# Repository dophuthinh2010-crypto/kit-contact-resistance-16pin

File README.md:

# Kit: 16-pin connector contact resistance tester

Test kit that measures the mated contact resistance of all 16 contacts of an
ITW McMurdo Red Range 16-way connector (RP16-T plug / RS16P-T socket) after
every plug/unplug cycle. The data is used to estimate connector life
(datasheet: 5 mΩ max initially, 10 mΩ max after conditioning, 500 mechanical operations).

**Status:** design stage, for review. Firmware and desktop app written (app core tested; firmware and GUI not yet run on hardware). Schematic and PCB layout not yet drawn in KiCad.

## How it works

- ESP32 selects one contact at a time (16 low-side MOSFETs driven by 2 × 74HC595).
- An LM317T constant-current source drives 0.625 A through the selected contact; a 0.1 Ω shunt read by
  the ADS1115 gives the current I. (Main board rev C.)
- Kelvin sense taps at the connector pads go through two 16-to-1 trees of CD4053BE switches straight to
  the ADS1115, read differentially at ±0.256 V (7.8 µV per step): contact voltage V.
- R = V / I. Range is about 0–51 mΩ (G = 101) or 0–470 mΩ (G = 11, jumper).
- One CSV line per pin per cycle over USB serial: `cycle, pin, I_A, V_mV, R_mOhm`.

Boards: main board (100 × 80 mm, 2-layer) plus two jack breakouts (about 80 × 40 mm),
linked by 34-way IDC ribbons (16 force + 16 sense + 2 GND).

## Repository layout

| Path | Contents |
| --- | --- |
| `docs/INSTALL.md` | **Start here:** installing the USB driver, the desktop app and the firmware, then running a test |
| `docs/design.md` | Design summary: schematic blocks, pin map, connector pinouts, layout rules, open items |
| `docs/concept_sketch.jpg` | System concept diagram (redrawn from the original sketch, `docs/concept_sketch_original.jpg`; source: `hardware/scripts/draw_concept_diagram.py`) |
| `docs/footprint_preview.png` | Preview of the connector footprints |
| `docs/CR-TEST_presentation.pptx` | 13-slide PowerPoint presentation of the kit (source: `docs/presentation/build_deck.js`, pptxgenjs) |
| `docs/3d-model/index.html` | Interactive 3D model of the kit (open in a browser; loads three.js from a CDN) |
| `docs/fault-protection.md` | Open/short fault review, isolation test, rev C protection, scenario results |
| `docs/serial-protocol.md` | Serial protocol between the ESP32 and the laptop |
| `firmware/crkit_esp32/` | ESP32 firmware (Arduino): scan, mate detect, calibration |
| `desktop-app/` | Desktop app (Python, PySide6): connect, record to CSV, live table and plot |
| `docs/simulation/index.html` | 3D simulation: plug/unplug cycles, 16-pin scan through the rev C LM317T / CD4053B / ADS1115 chain with noise, assumed wear model and life estimate |
| `hardware/BOM.xlsx`, `hardware/BOM.csv` | Bill of materials for one kit (rev C, $156.22): model, supplier, price, alternative part (shared sheet: https://claude.ai/artifact/EmcHuasxRLR5GvdHxSPXVu) |
| `hardware/kicad/` | **Rev C KiCad 8 projects**: main board (schematic + placed PCB), female and male jack boards, shared libraries, previews. Not routed yet: see `hardware/kicad/README.md` |
| `hardware/scripts/kicad_gen/` | Python generator for those projects (`python build_all.py`) |
| `hardware/footprints/McMurdo_RedRange.pretty/` | KiCad footprints for RP16-T and RS16P-T |
| `hardware/scripts/gen_mcmurdo_fp.py` | Script that generates those footprints |

The full, living design document (with the BOM and block diagram) is the Claude doc
"PCB Design – 16-Pin Blindmate Contact Resistance Test Kit":
https://claude.ai/artifact/T8kFqe1HFXj3PjpiL8ypHh

## Connector reference

ITW McMurdo "Red range" industrial rack and panel connectors datasheet (not included in
this repo; get it from ITW McMurdo or a distributor).

## Using the footprints

KiCad → Preferences → Manage Footprint Libraries → add
`hardware/footprints/McMurdo_RedRange.pretty`.

## Next steps

- [ ] Review the design summary and open items
- [x] Schematic rev C in KiCad (LM317T, CD4053BE, ADS1115; main board + jack boards, generated)
- [x] PCB placement, nets, net classes, outlines, GND pours
- [ ] Open in KiCad 8, run ERC/DRC, route (hand-route power, Freerouting for the rest)
- [ ] Check footprints against real parts, then order PCBs
- [x] Firmware: scan loop, calibration, serial protocol
- [x] Desktop app: recording, live view, resume, summary
- [ ] Test firmware and app on the real kit

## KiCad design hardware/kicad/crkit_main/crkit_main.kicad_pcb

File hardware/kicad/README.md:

# KiCad projects, board rev C

| Folder | Board | Size | Status |
| --- | --- | --- | --- |
| `crkit_main/` | Main board: LM317T current source, 16 pin switches, 10× CD4053BE sense muxes, ADS1115, ESP32-DevKitC socket | 135 × 101 mm, 2 layers, 2 oz | Schematic complete. PCB placed, nets and net classes set, GND pours on both layers. **Not routed** |
| `crkit_jack_female/` | RS16P-T socket + 2×17 IDC | 80 × 40 mm | Schematic complete. PCB placed. **Not routed** |
| `crkit_jack_male/` | RP16-T plug + 2×17 IDC | 80 × 40 mm | Schematic complete. PCB placed. **Not routed** |
| `crkit.kicad_sym`, `crkit.pretty/` | Symbols and footprints used by all three (also embedded in each file) | | |
| `preview/` | PNG previews of the schematic and of each placement with its ratsnest | | |

All files are written by `hardware/scripts/kicad_gen/build_all.py` (KiCad 8 format). The design lives
in the scripts: `main_board.py` (netlist + placement), `jack_board.py`, `lib.py` (symbols and footprints).
To change the design, edit the script and run `python build_all.py`, or open the files in KiCad and keep
editing there (then stop regenerating, or your KiCad edits will be overwritten).

The files were generated without KiCad (no KiCad in the build environment). They follow the KiCad 8 file
format and pass a structural check, but **open them in KiCad 8 or newer and run ERC and DRC before
anything else.** Schematic style: every part is a box symbol, and every pin ends in a short wire with
a net label, so the netlist is exact and easy to check against `docs/design.md`.

## Rev C changes (23 Nov 2026)

| Change | Parts |
| --- | --- |
| Test current from an **LM317T** constant-current source: R_SET 2.0 Ω 3 W → 0.625 A. Replaces R_HI, R_LO and the ACS712 | U2, R4, C4, C5 |
| Current measured on a **0.1 Ω 1 % shunt** (2512) by the ADS1115 (AIN2−AIN3, Kelvin taps) | R5, R74, R75, C19 |
| Sense muxes: two 16-to-1 trees of **CD4053BE** (15 switches each: S0 / S1 / S2 / S3 by level) replace the CD74HC4067s | U5–U9 (female), U10–U14 (male), C8–C17 |
| **INA333, OPA333 REF buffer and gain jumper removed**: the ADS1115 reads the contact differentially at ±0.256 V | U15, R72, R73, C18, D3, D4 |
| 32 BAT54S input clamps removed: 10 kΩ per sense line into the 3.3 V muxes (bleeder R70), clamps only at the ADC | R38–R70 |
| 5 V monitor moved from ADS1115 AIN2 to ESP32 IO34 | R79, R80, C21 |
| Board 135 × 90 → 135 × 101 mm | |

Rev B changes still in place: reverse-polarity MOSFET (Q1), 10 kΩ sense resistors, 3.3 kΩ bleeder,
ribbon pins 33/34 not connected.

## Reference map (docs → KiCad references)

| Docs | KiCad | Docs | KiCad |
| --- | --- | --- | --- |
| Q_REV | Q1 | Q_DRV 2N7002 | Q2 |
| Q_EN AO3401A | Q3 | Pin switches 1…16 | Q4…Q19 (contact n = Q(n+3)) |
| LM317T | U2 | R_SET 2.0 Ω / R_SH 0.1 Ω | R4 / R5 |
| AP2112K LDO | U1 | 74HC595 ×2 | U3, U4 |
| CD4053BE female tree | U5–U9 | CD4053BE male tree | U10–U14 |
| ADS1115 | U15 | ESP32-DevKitC | U16 |
| Barrel jack | J1 | IDC to female / male board | J2 / J3 |
| Mate switch | J4 | I²C spare | J5 |
| Sense resistors 10 k | R38–R69 | Test points | TP1 LO_RTN, TP2 GND, TP3 F_BUS, TP4 SENSE_F, TP5 SENSE_M, TP6 V5_MON |

## Main board placement

- Top: LM317T (U2, vertical TO-220 with a clip-on heatsink), R_SET (R4, mount 2 mm off the board),
  current switch Q2/Q3, shunt R5, shift registers U3/U4.
- Left: power input (J1 on the board edge, Q1 reverse protection, F1, D2 TVS, C1, LDO U1).
- Centre: two rows of 8 pin switches with their gate resistors and pull-downs.
- Middle: ADS1115 (U15) with its input filters and clamps, pull-ups, 5 V monitor, test points.
- Lower: one row of ten CD4053BE, female tree on the left (U5–U9), male tree on the right (U10–U14),
  a 100 nF decoupler beside each.
- Bottom: 10 k sense resistors straight above their IDC columns. J2/J3 are turned 180° so the sense row
  faces the resistors. **Pin 1 is at the right-hand end** of both headers.
- Right: ESP32-DevKitC on two 1×19 sockets 25.4 mm apart, USB end over the top edge.

## Routing (next step)

Net classes are set in the project: **Power** 1.0 mm / 0.3 mm (F_BUS, LO_RTN, I_HI, ACS_IP, +5V, VIN_*,
MF1–MF16, GND, LM_IN, LM_OUT) and **Sense** 0.25 mm (SF/SM, SFC/SMC, tree nodes, SENSE_F/M, ADS and shunt taps). Default 0.25 mm / 0.2 mm.

1. Open `crkit_main.kicad_pro` in KiCad 8+. Run **Inspect → Electrical Rules Checker** on the schematic, then
   **Tools → Update PCB from Schematic** (should report no changes) and **DRC** (unrouted only).
2. Route by hand first: F_BUS (R_SET/LM317T ADJ → J2 odd row) and LO_RTN (16 sources → R5) as wide pours or 1.5 mm
   traces on the top layer; the R5 return goes straight to the J1 ground, and the two R5 ADC taps are separate thin traces.
3. Then autoroute the rest: **File → Export → Specctra DSN**, route it in Freerouting, then
   **File → Import → Specctra Session**. Keep SENSE_F and SENSE_M as a tight pair over unbroken ground.
4. Press **B** to refill the GND pours and run DRC again.
5. Jack boards: the force (odd) and sense (even) trace of each contact must leave the pad on opposite sides
   and meet only at the pad. Contacts 9–16 are on the far row, so use both layers.

## Check before ordering PCBs

- Footprints against real parts: RP16-T / RS16P-T sample, CUI PJ-002A barrel jack drawing,
  your ESP32-DevKitC (row spacing 25.4 mm, pinout of V4), the LM317T heatsink outline, the 3 W R_SET lead spacing.
- ERC, DRC, and a 1:1 paper print of each board with the connector and the DevKitC laid on it.

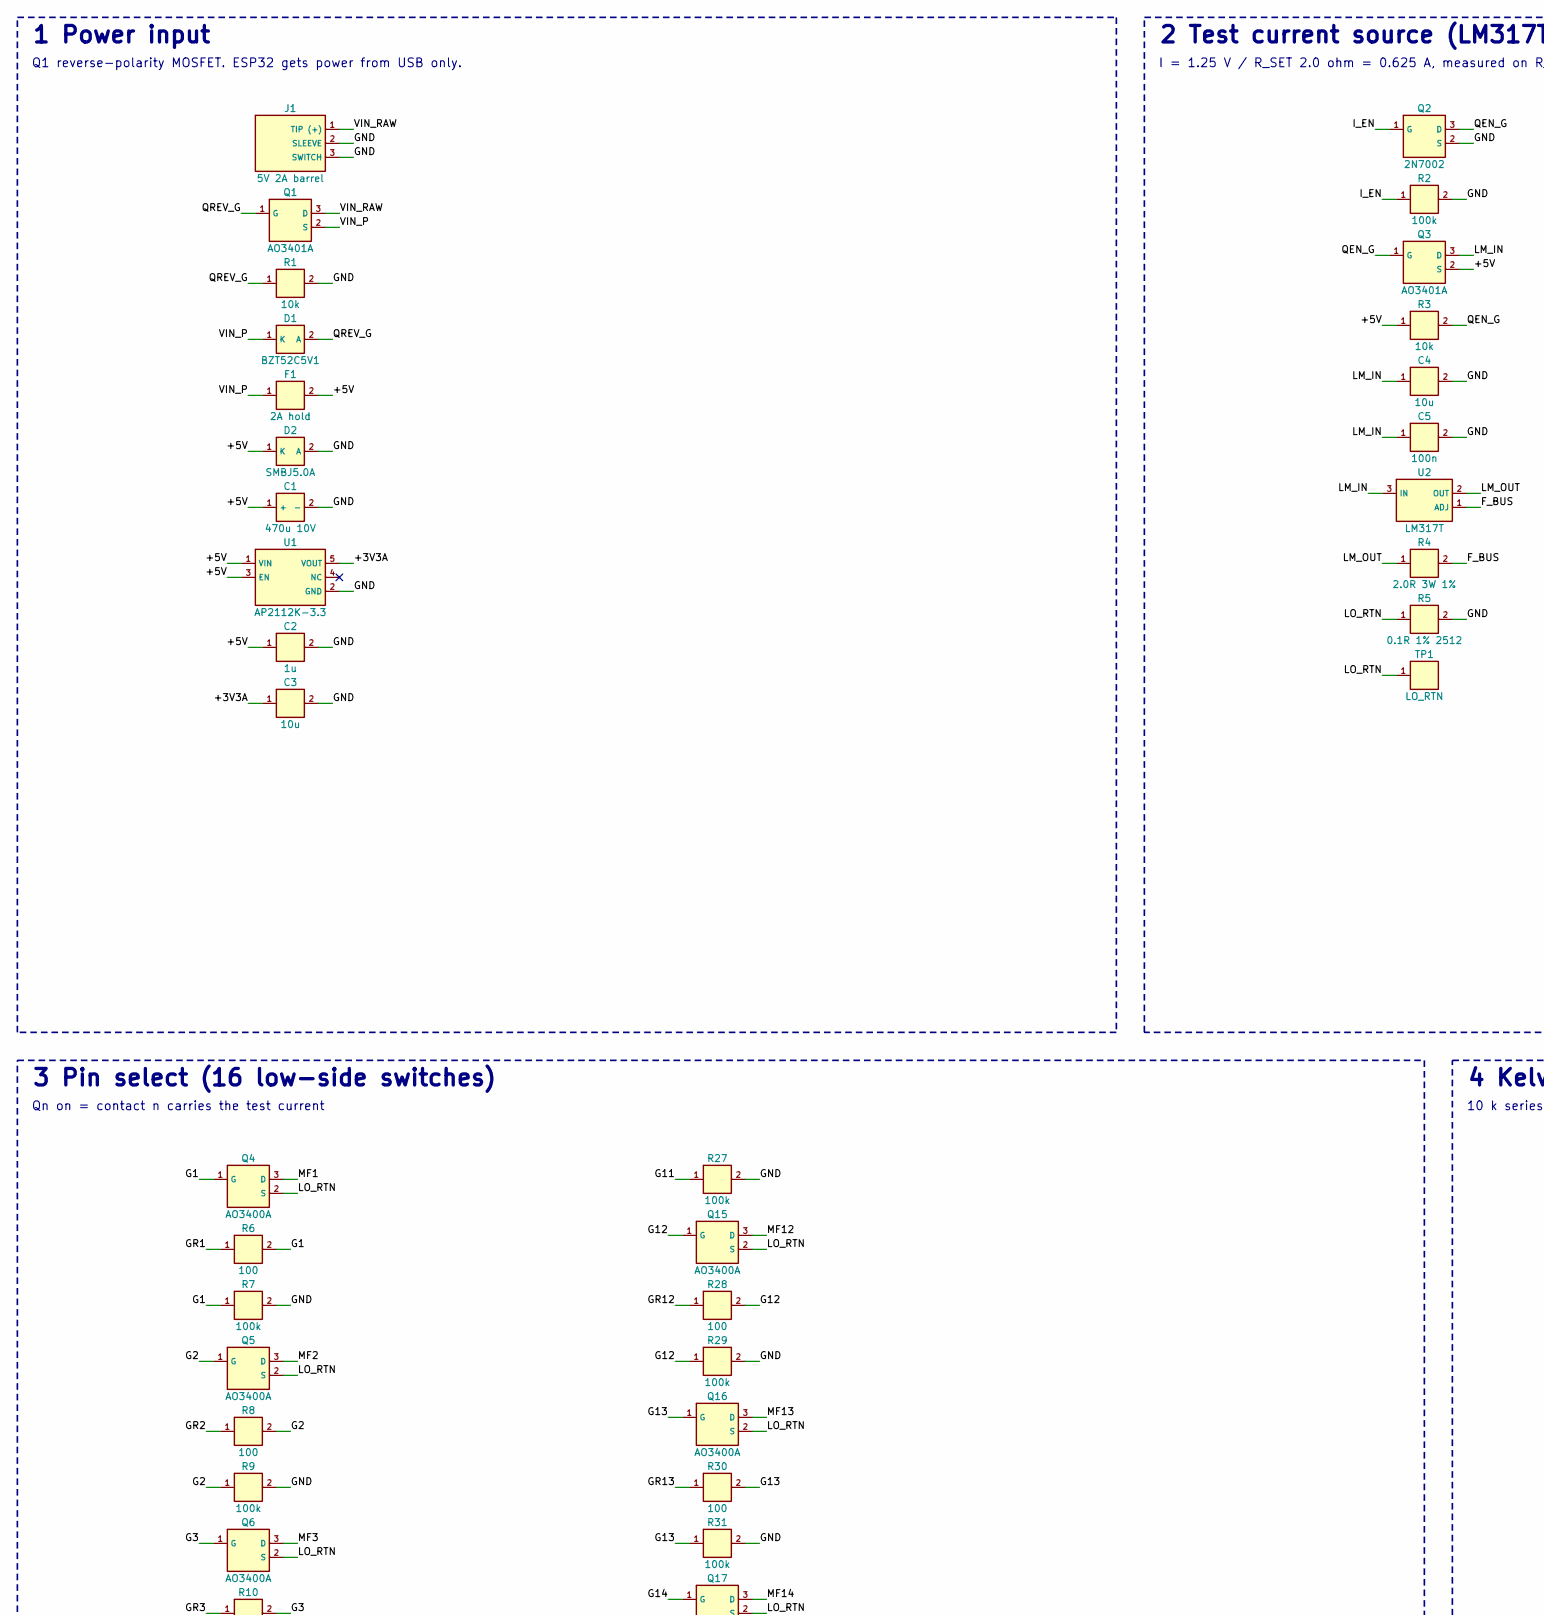
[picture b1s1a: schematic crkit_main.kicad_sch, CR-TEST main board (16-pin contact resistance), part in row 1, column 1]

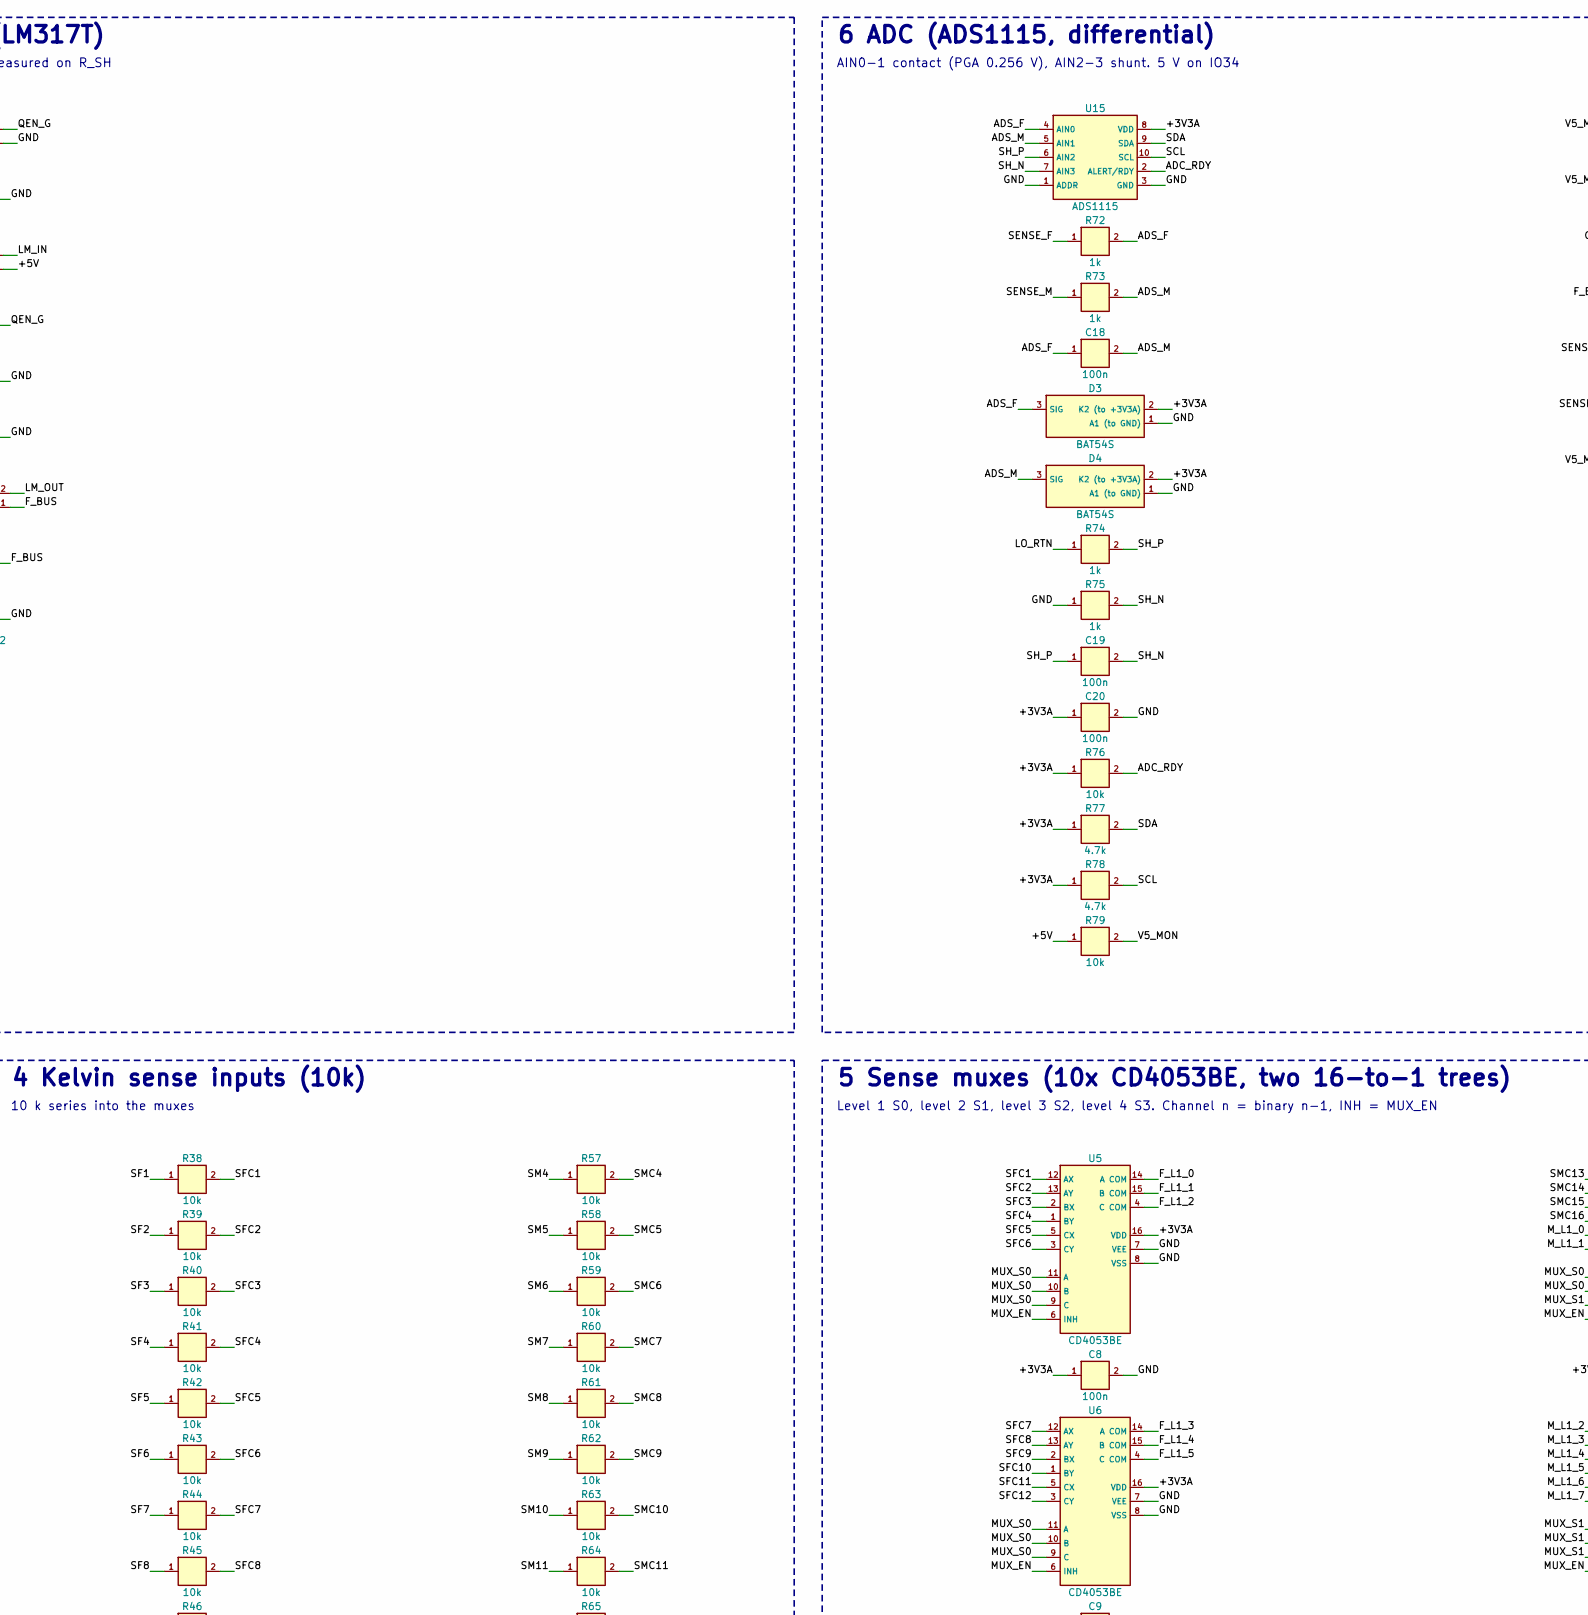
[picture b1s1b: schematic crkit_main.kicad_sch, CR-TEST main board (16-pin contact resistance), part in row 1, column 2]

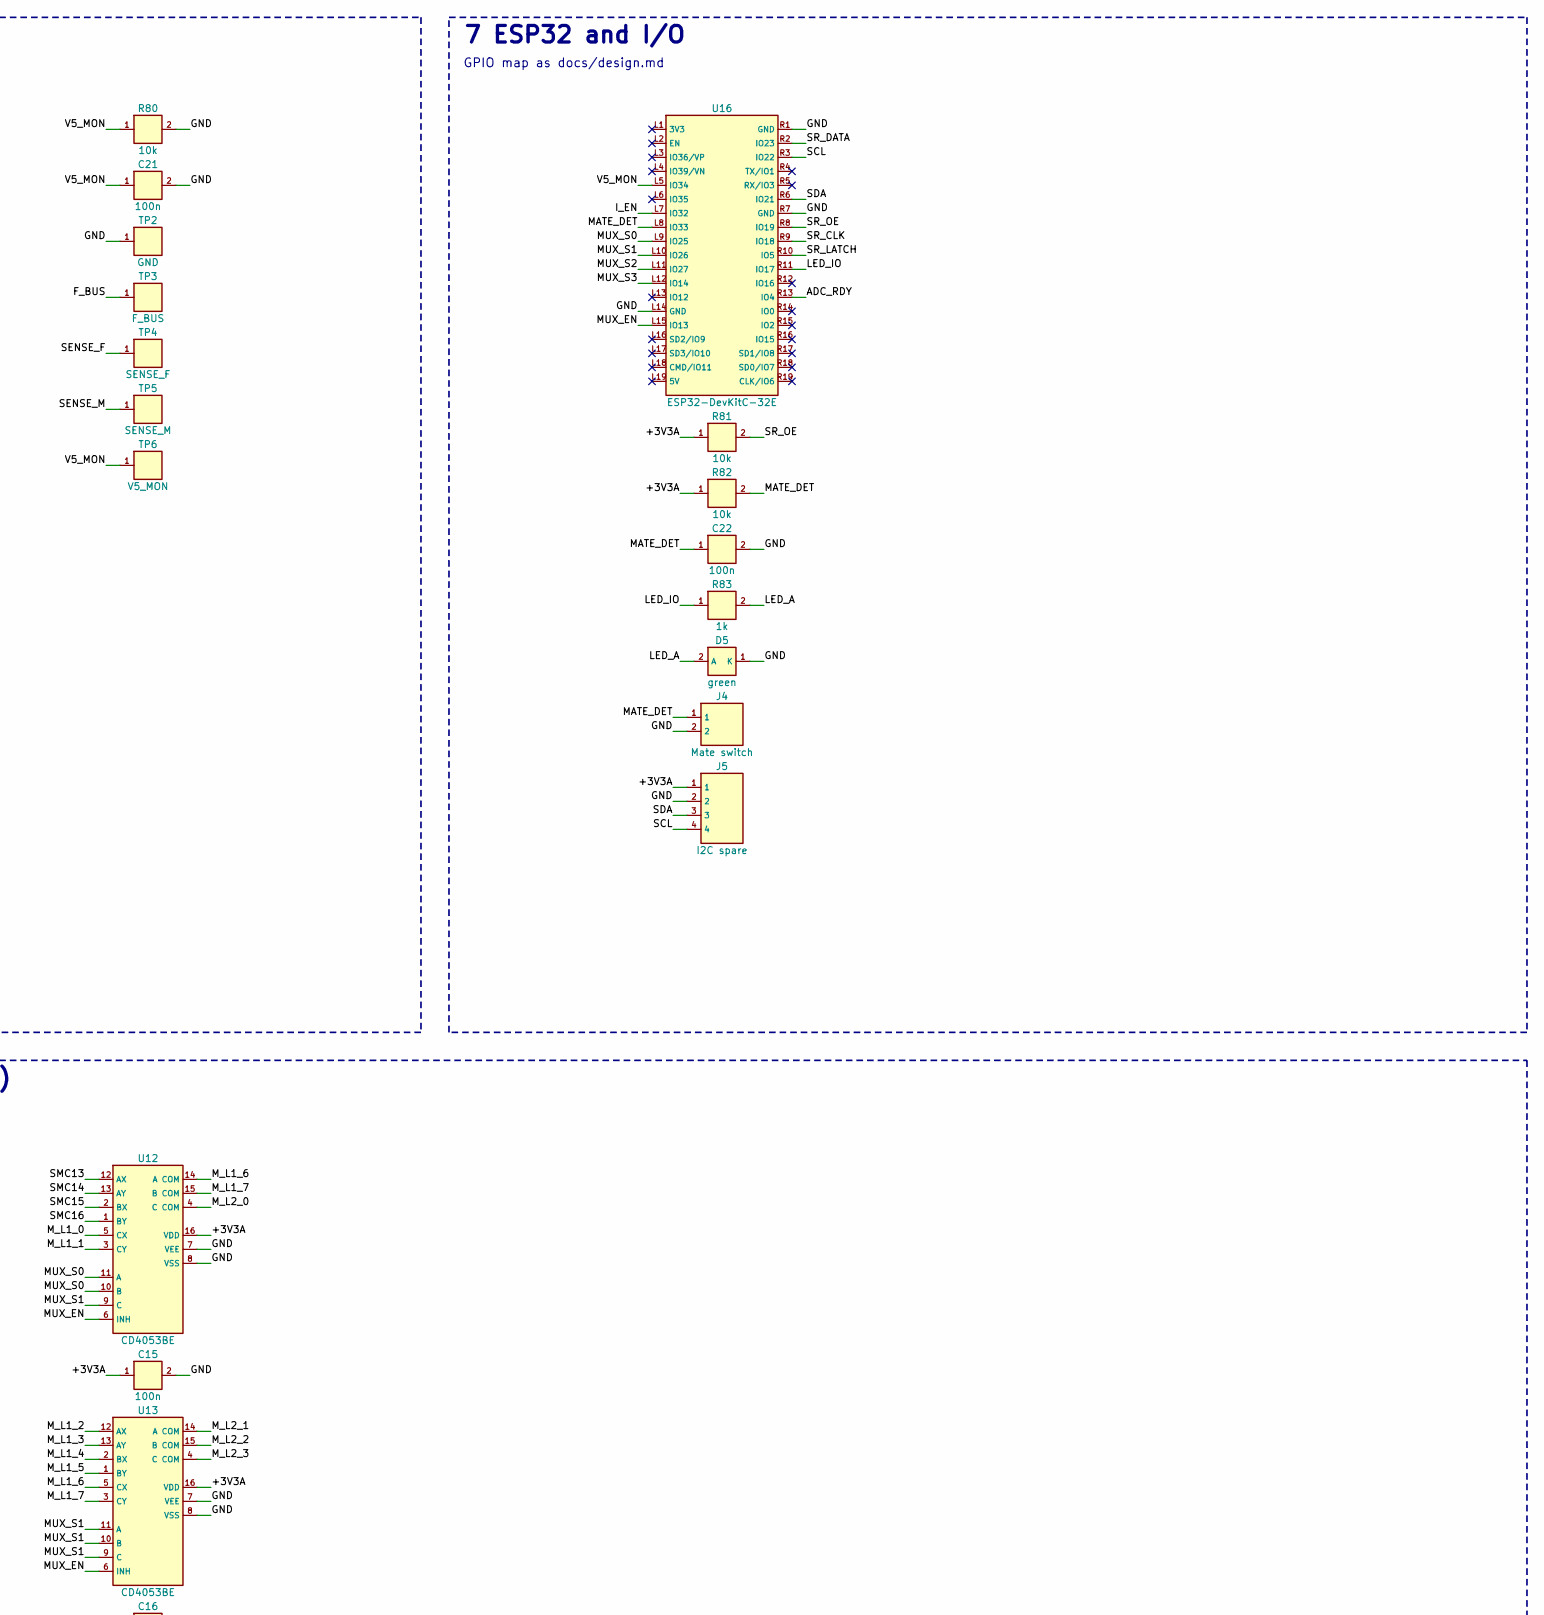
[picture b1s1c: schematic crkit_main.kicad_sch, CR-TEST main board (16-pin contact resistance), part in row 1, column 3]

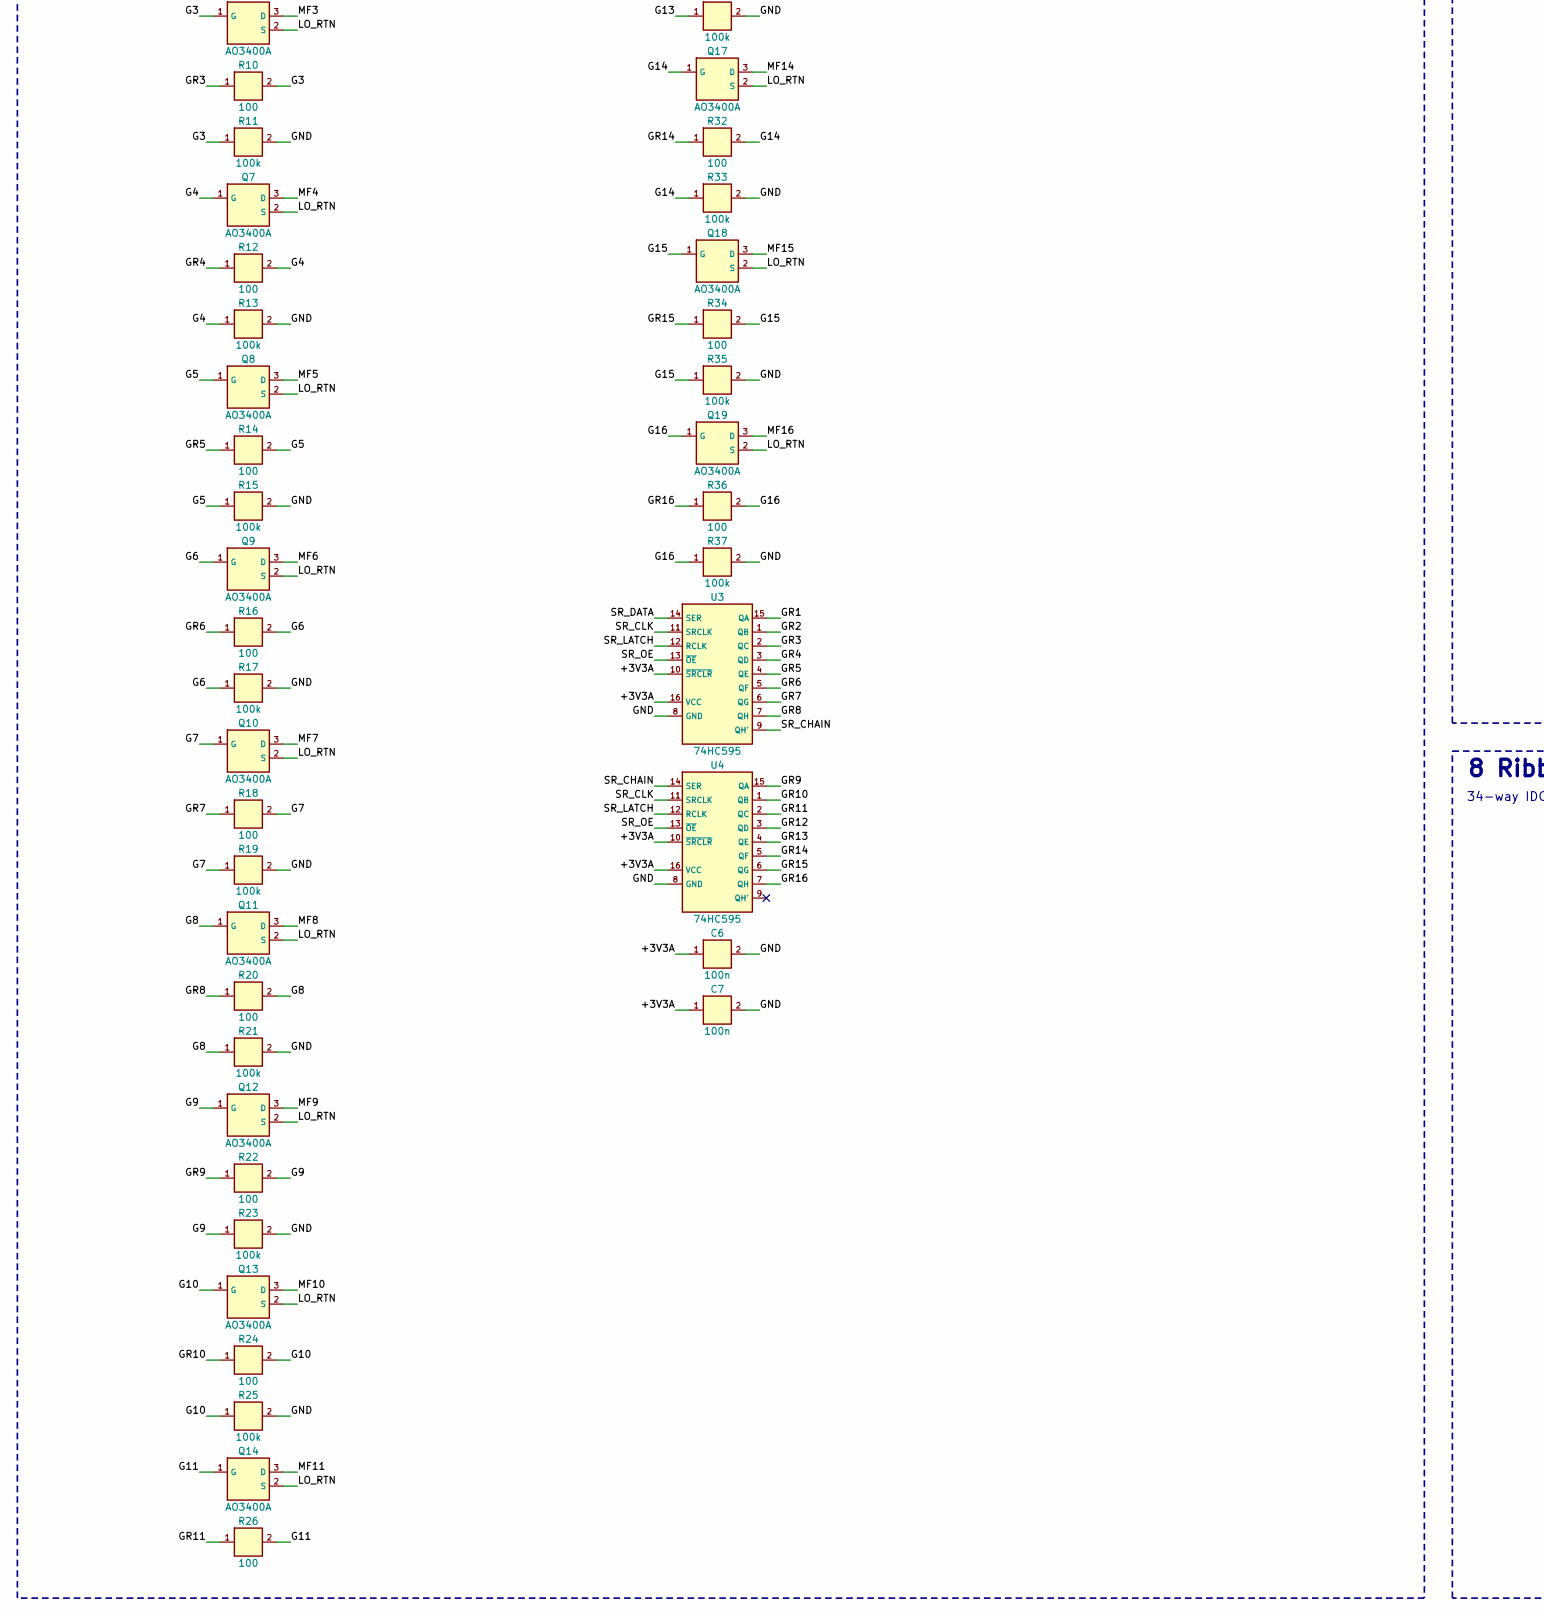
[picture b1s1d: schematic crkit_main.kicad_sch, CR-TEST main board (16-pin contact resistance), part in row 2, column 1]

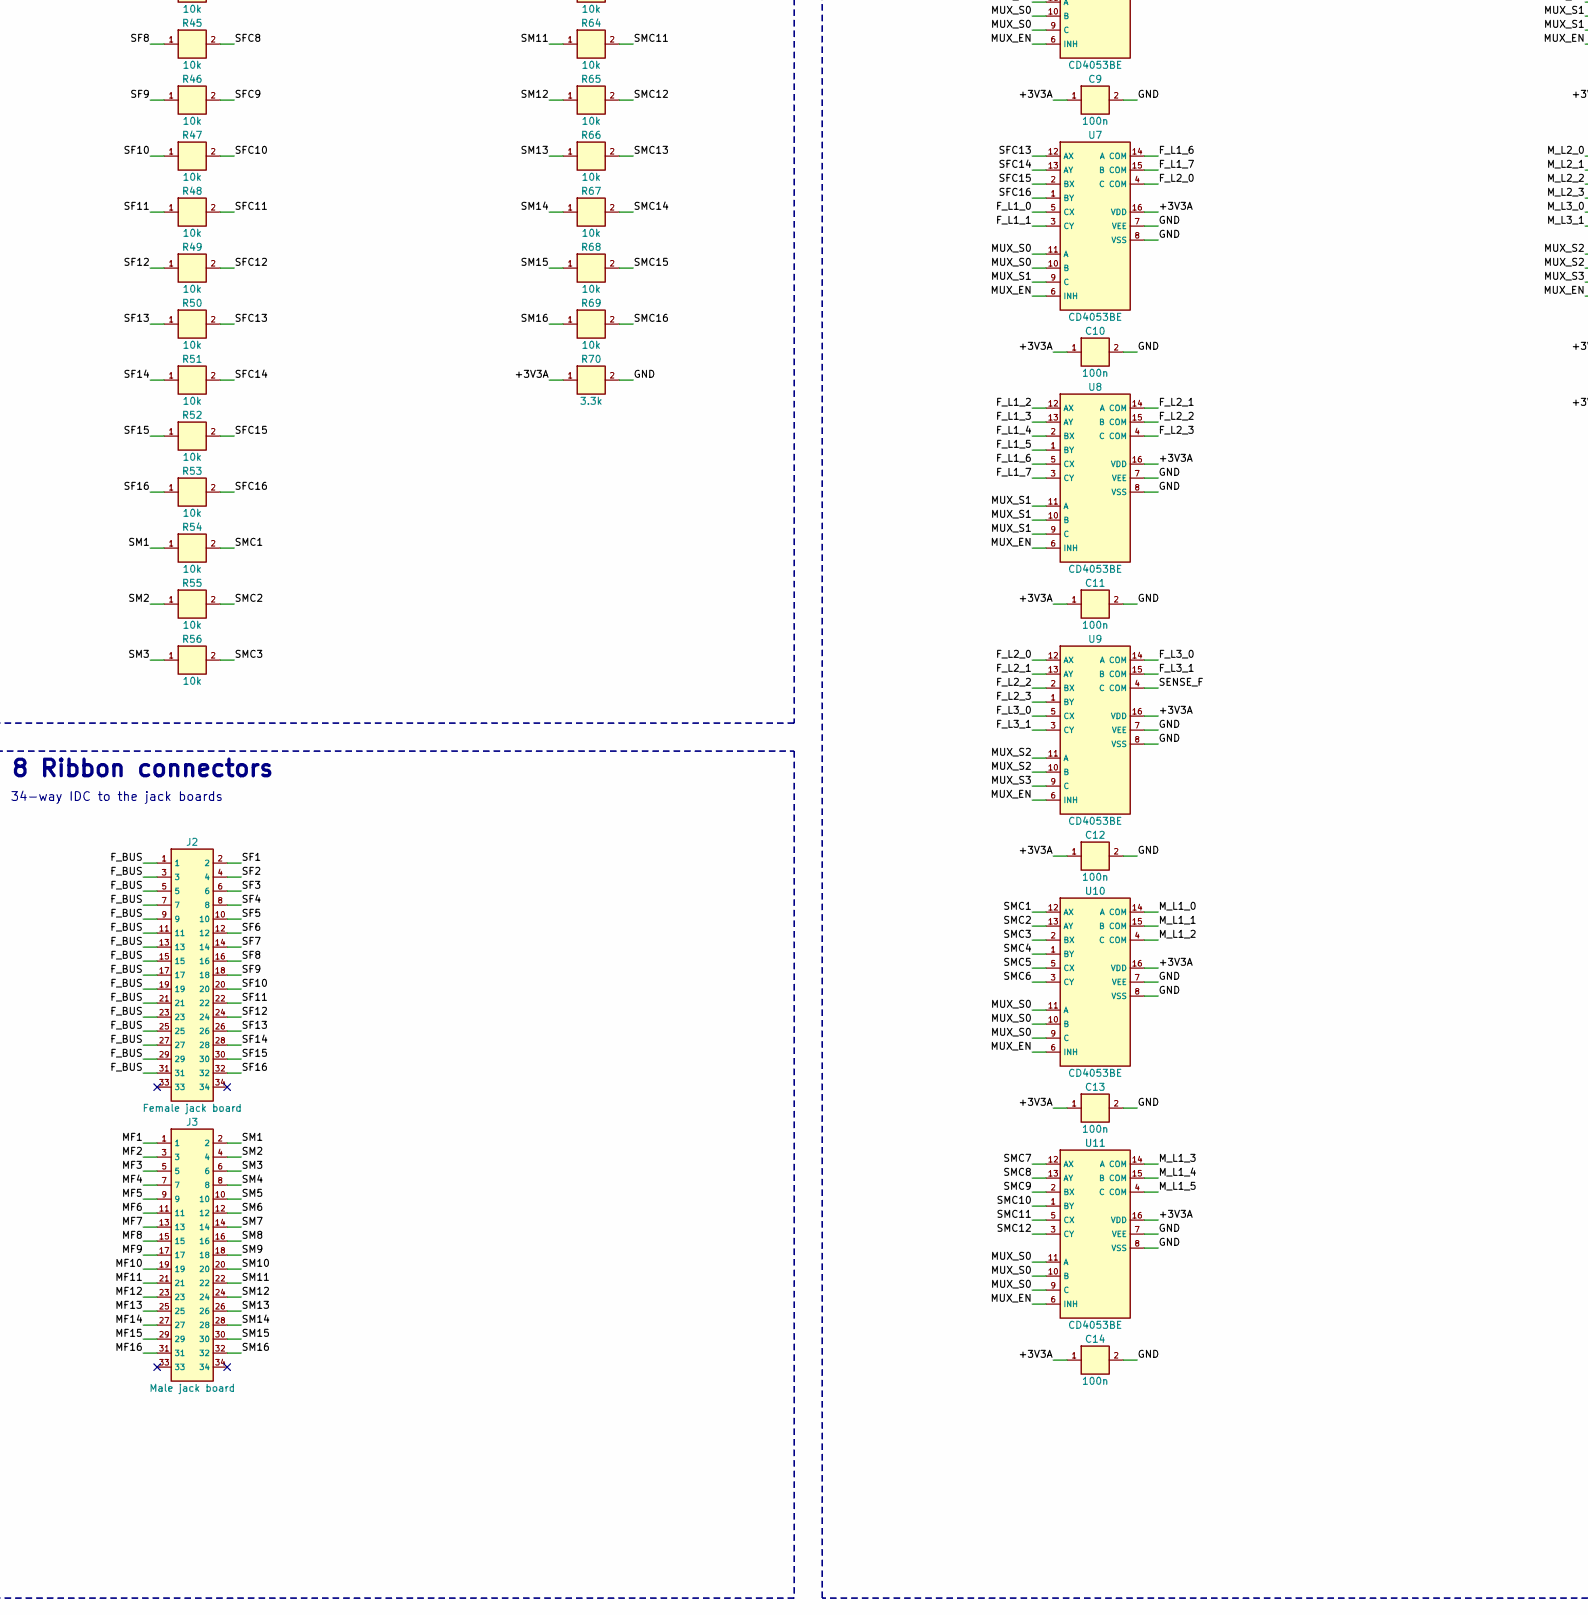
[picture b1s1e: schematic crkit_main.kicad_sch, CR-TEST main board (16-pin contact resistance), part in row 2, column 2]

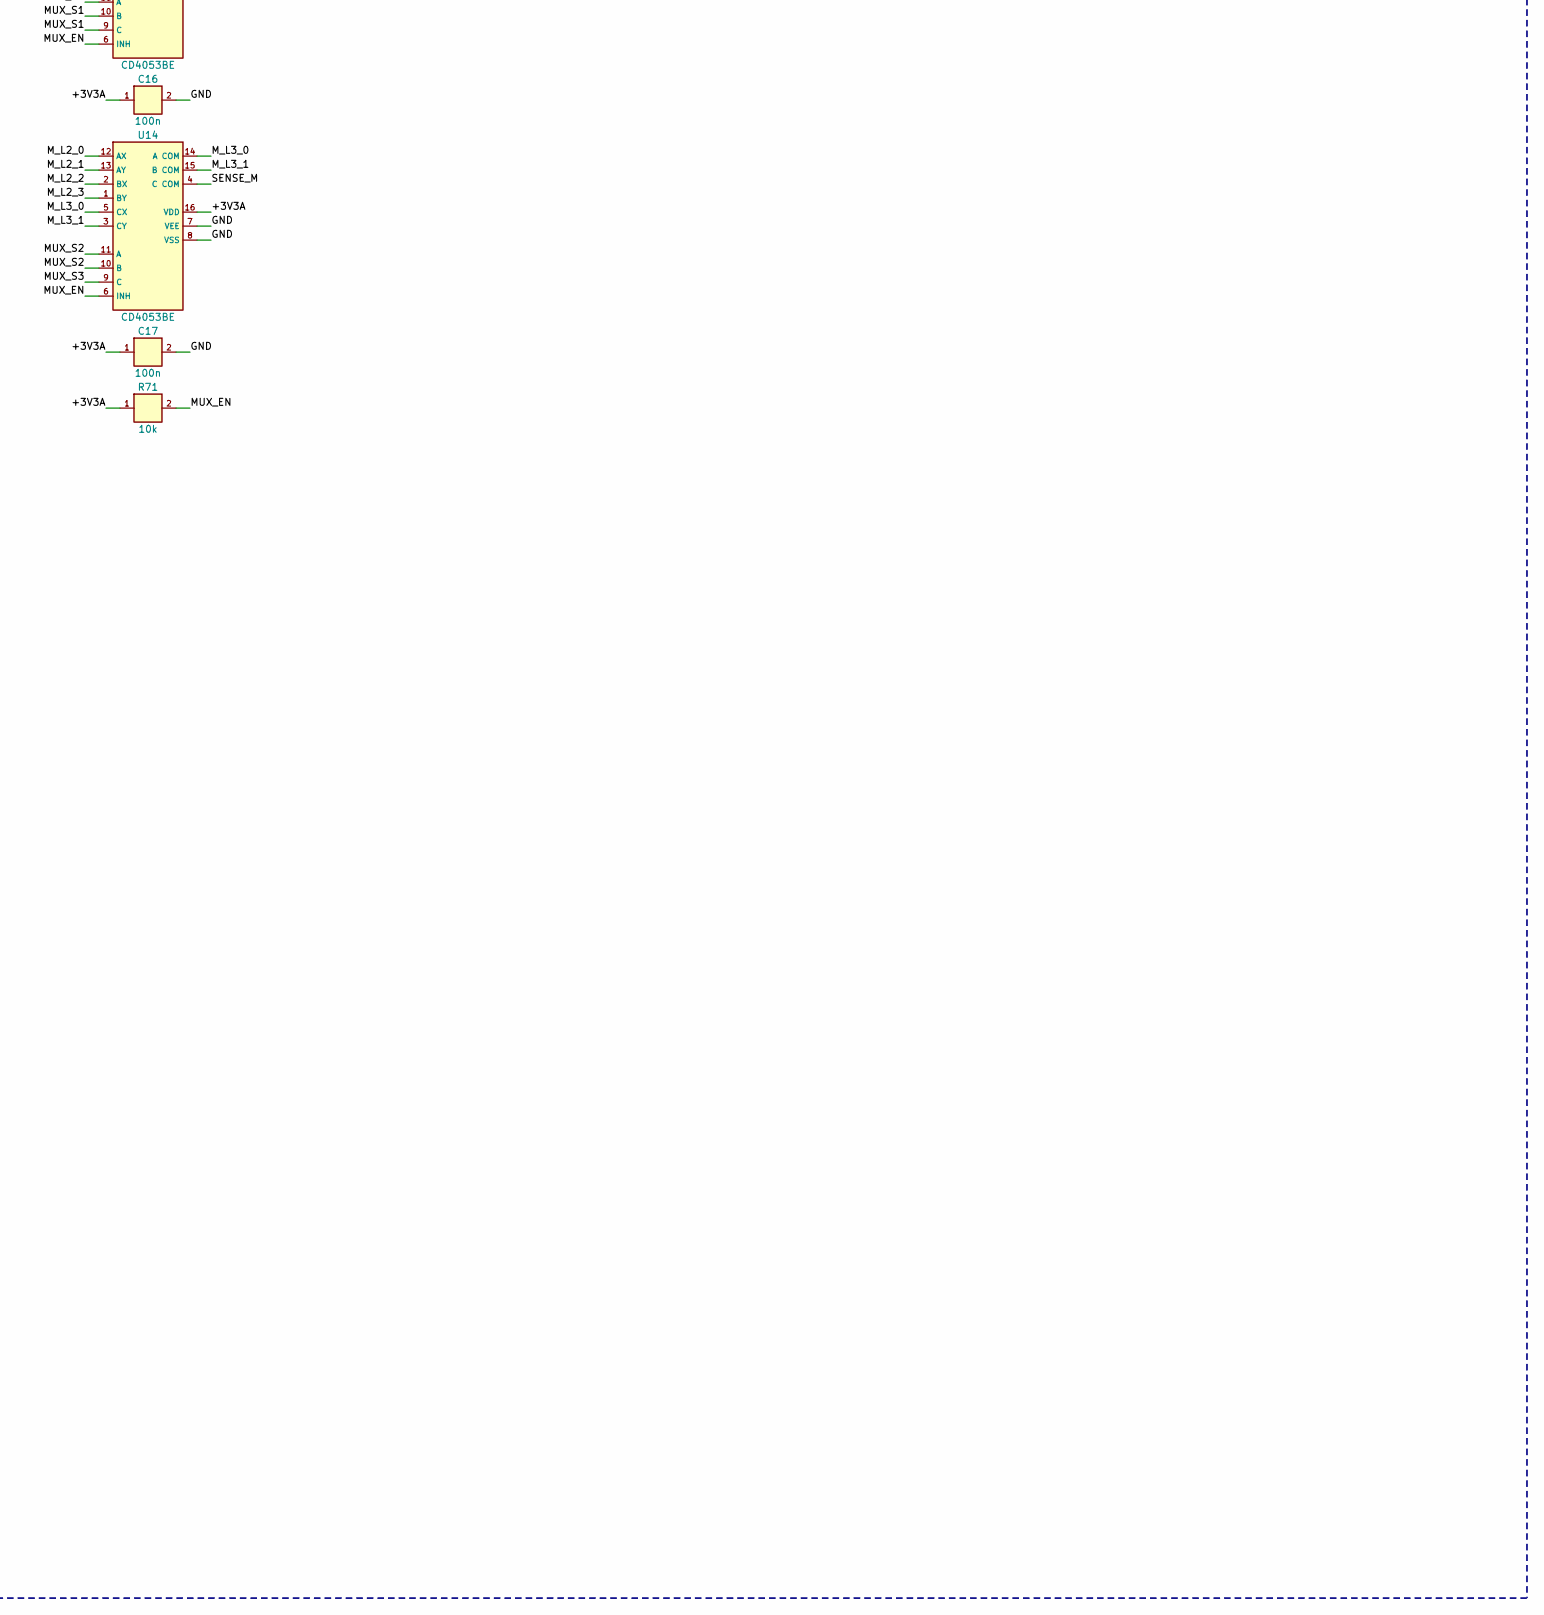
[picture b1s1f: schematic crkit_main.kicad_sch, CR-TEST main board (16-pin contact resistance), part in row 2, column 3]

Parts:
C1: 470u 10V; CP_Radial_D8.0mm_P3.50mm; MPN Panasonic EEU-FR1A471
C2: 1u; C_0805_2012Metric; MPN Samsung CL21 X7R
C3, C4: 10u; C_0805_2012Metric; MPN Samsung CL21 X5R
C5, C6, C7, C8, C9, C10, C11, C12, C13, C14, C15, C16, C17, C18, C19, C20, C21, C22: 100n; C_0603_1608Metric; MPN Samsung CL10 X7R
D1: BZT52C5V1; D_SOD-123; MPN Diodes BZT52C5V1
D2: SMBJ5.0A; D_SMB; MPN Littelfuse SMBJ5.0A
D3, D4: BAT54S; SOT-23; MPN Nexperia BAT54S
D5: green; LED_0805_2012Metric; MPN 0805 green LED
F1: 2A hold; Fuse_1812_4532Metric; MPN Bourns MF-MSMF200-2
J1: 5V 2A barrel; BarrelJack_CUI_PJ-002A_Horizontal; MPN CUI PJ-002A
J2: Female jack board; IDC-Header_2x17_P2.54mm_Vertical; MPN Amphenol T821134A1S100CEU
J3: Male jack board; IDC-Header_2x17_P2.54mm_Vertical; MPN Amphenol T821134A1S100CEU
J4: Mate switch; JST_XH_B2B-XH-A_1x02_P2.50mm_Vertical; MPN JST B2B-XH-A
J5: I2C spare; PinHeader_1x04_P2.54mm_Vertical; MPN 2.54 mm header
Q1, Q3: AO3401A; SOT-23; MPN AOS AO3401A
Q2: 2N7002; SOT-23; MPN 2N7002
Q4, Q5, Q6, Q7, Q8, Q9, Q10, Q11, Q12, Q13, Q14, Q15, Q16, Q17, Q18, Q19: AO3400A; SOT-23; MPN AOS AO3400A
R1, R3, R38, R39, R40, R41, R42, R43, R44, R45, R46, R47, R48, R49, R50, R51, R52, R53, R54, R55, R56, R57, R58, R59, R60, R61, R62, R63, R64, R65, R66, R67, R68, R69, R71, R76, R79, R80, R81, R82: 10k; R_0603_1608Metric; MPN UNI-ROYAL 0603WAF
R2, R7, R9, R11, R13, R15, R17, R19, R21, R23, R25, R27, R29, R31, R33, R35, R37: 100k; R_0603_1608Metric; MPN UNI-ROYAL 0603WAF
R4: 2.0R 3W 1%; R_Axial_3W_L15.5mm_P20.32mm; MPN Vishay PR03000202008JAC00 (or any 2.0 o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
R5: 0.1R 1% 2512; R_2512_6332Metric_Shunt; MPN Yageo PE2512FKF070R1L
R6, R8, R10, R12, R14, R16, R18, R20, R22, R24, R26, R28, R30, R32, R34, R36: 100; R_0603_1608Metric; MPN UNI-ROYAL 0603WAF
R70: 3.3k; R_0603_1608Metric; MPN UNI-ROYAL 0603WAF
R72, R73, R74, R75, R83: 1k; R_0603_1608Metric; MPN UNI-ROYAL 0603WAF
R77, R78: 4.7k; R_0603_1608Metric; MPN UNI-ROYAL 0603WAF
TP1: LO_RTN; TestPoint_THTPad_D2.0mm_Drill1.0mm
TP2: GND; TestPoint_THTPad_D2.0mm_Drill1.0mm
TP3: F_BUS; TestPoint_THTPad_D2.0mm_Drill1.0mm
TP4: SENSE_F; TestPoint_THTPad_D2.0mm_Drill1.0mm
TP5: SENSE_M; TestPoint_THTPad_D2.0mm_Drill1.0mm
TP6: V5_MON; TestPoint_THTPad_D2.0mm_Drill1.0mm
U1: AP2112K-3.3; SOT-23-5; MPN Diodes AP2112K-3.3TRG1
U2: LM317T; TO-220-3_Vertical_Heatsink; MPN TI LM317T (TO-220) + clip-on heatsink
U3, U4: 74HC595; SOIC-16_3.9x9.9mm_P1.27mm; MPN TI SN74HC595DR
U5, U6, U7, U8, U9, U10, U11, U12, U13, U14: CD4053BE; DIP-16_W7.62mm; MPN TI CD4053BE
U15: ADS1115; VSSOP-10_3.0x3.0mm_P0.5mm; MPN TI ADS1115IDGSR
U16: ESP32-DevKitC-32E; ESP32-DevKitC_V4_Socket_2x1x19_25.4mm; MPN Espressif ESP32-DevKitC-32E on 2x 1x19 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

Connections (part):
+3V3A: C3.1, C6.1, C7.1, C8.1, C9.1, C10.1, C11.1, C12.1, C13.1, C14.1, C15.1, C16.1, C17.1, C20.1, D3.2 (K2 (to +3V3A)), D4.2 (K2 (to +3V3A)), J5.1, R70.1, R71.1, R76.1, R77.1, R78.1, R81.1, R82.1, U1.5 (VOUT), U3.10 (~SRCLR), U3.16 (VCC), U4.10 (~SRCLR), U4.16 (VCC), U5.16 (VDD), U6.16 (VDD), U7.16 (VDD), U8.16 (VDD), U9.16 (VDD), U10.16 (VDD), U11.16 (VDD), U12.16 (VDD), U13.16 (VDD), U14.16 (VDD), U15.8 (VDD)
+5V: C1.1 (+), C2.1, D2.1 (K), F1.2, Q3.2 (S), R3.1, R79.1, U1.1 (VIN), U1.3 (EN)
ADC_RDY: R76.2, U15.2 (ALERT/RDY), U16.R13 (IO4)
ADS_F: C18.1, D3.3 (SIG), R72.2, U15.4 (AIN0)
ADS_M: C18.2, D4.3 (SIG), R73.2, U15.5 (AIN1)
F_BUS: J2.1, J2.3, J2.5, J2.7, J2.9, J2.11, J2.13, J2.15, J2.17, J2.19, J2.21, J2.23, J2.25, J2.27, J2.29, J2.31, R4.2, TP3.1, U2.1 (ADJ)
F_L1_0: U5.14 (A COM), U7.5 (CX)
F_L1_1: U5.15 (B COM), U7.3 (CY)
F_L1_2: U5.4 (C COM), U8.12 (AX)
F_L1_3: U6.14 (A COM), U8.13 (AY)
F_L1_4: U6.15 (B COM), U8.2 (BX)
F_L1_5: U6.4 (C COM), U8.1 (BY)
F_L1_6: U7.14 (A COM), U8.5 (CX)
F_L1_7: U7.15 (B COM), U8.3 (CY)
F_L2_0: U7.4 (C COM), U9.12 (AX)
F_L2_1: U8.14 (A COM), U9.13 (AY)
F_L2_2: U8.15 (B COM), U9.2 (BX)
F_L2_3: U8.4 (C COM), U9.1 (BY)
F_L3_0: U9.5 (CX), U9.14 (A COM)
F_L3_1: U9.3 (CY), U9.15 (B COM)
G1: Q4.1 (G), R6.2, R7.1
G2: Q5.1 (G), R8.2, R9.1
G3: Q6.1 (G), R10.2, R11.1
G4: Q7.1 (G), R12.2, R13.1
G5: Q8.1 (G), R14.2, R15.1
G6: Q9.1 (G), R16.2, R17.1
G7: Q10.1 (G), R18.2, R19.1
G8: Q11.1 (G), R20.2, R21.1
G9: Q12.1 (G), R22.2, R23.1
G10: Q13.1 (G), R24.2, R25.1
G11: Q14.1 (G), R26.2, R27.1
G12: Q15.1 (G), R28.2, R29.1
G13: Q16.1 (G), R30.2, R31.1
G14: Q17.1 (G), R32.2, R33.1
G15: Q18.1 (G), R34.2, R35.1
G16: Q19.1 (G), R36.2, R37.1
GND: C1.2 (-), C2.2, C3.2, C4.2, C5.2, C6.2, C7.2, C8.2, C9.2, C10.2, C11.2, C12.2, C13.2, C14.2, C15.2, C16.2, C17.2, C20.2, C21.2, C22.2, D2.2 (A), D3.1 (A1 (to GND)), D4.1 (A1 (to GND)), D5.1 (K), J1.2 (SLEEVE), J1.3 (SWITCH), J4.2, J5.2, Q2.2 (S), R1.2, R2.2, R5.2, R7.2, R9.2, R11.2, R13.2, R15.2, R17.2, R19.2, R21.2, R23.2, R25.2, R27.2, R29.2, R31.2, R33.2, R35.2, R37.2, R70.2, R75.1, R80.2, TP2.1, U1.2 (GND), U3.8 (GND), U4.8 (GND), U5.7 (VEE), U5.8 (VSS), U6.7 (VEE), U6.8 (VSS), U7.7 (VEE), U7.8 (VSS), U8.7 (VEE), U8.8 (VSS), U9.7 (VEE), U9.8 (VSS), U10.7 (VEE), U10.8 (VSS), U11.7 (VEE), U11.8 (VSS), U12.7 (VEE), U12.8 (VSS), U13.7 (VEE), U13.8 (VSS), U14.7 (VEE), U14.8 (VSS), U15.1 (ADDR), U15.3 (GND), U16.L14 (GND), U16.R1 (GND), U16.R7 (GND)
GR1: R6.1, U3.15 (QA)
GR2: R8.1, U3.1 (QB)
GR3: R10.1, U3.2 (QC)
GR4: R12.1, U3.3 (QD)
GR5: R14.1, U3.4 (QE)
GR6: R16.1, U3.5 (QF)
GR7: R18.1, U3.6 (QG)
GR8: R20.1, U3.7 (QH)
GR9: R22.1, U4.15 (QA)
GR10: R24.1, U4.1 (QB)
GR11: R26.1, U4.2 (QC)
GR12: R28.1, U4.3 (QD)
GR13: R30.1, U4.4 (QE)
GR14: R32.1, U4.5 (QF)
GR15: R34.1, U4.6 (QG)
GR16: R36.1, U4.7 (QH)
I_EN: Q2.1 (G), R2.1, U16.L7 (IO32)
LED_A: D5.2 (A), R83.2
LED_IO: R83.1, U16.R11 (IO17)
LM_IN: C4.1, C5.1, Q3.3 (D), U2.3 (IN)
LM_OUT: R4.1, U2.2 (OUT)
LO_RTN: Q4.2 (S), Q5.2 (S), Q6.2 (S), Q7.2 (S), Q8.2 (S), Q9.2 (S), Q10.2 (S), Q11.2 (S), Q12.2 (S), Q13.2 (S), Q14.2 (S), Q15.2 (S), Q16.2 (S), Q17.2 (S), Q18.2 (S), Q19.2 (S), R5.1, R74.1, TP1.1
MATE_DET: C22.1, J4.1, R82.2, U16.L8 (IO33)
MF1: J3.1, Q4.3 (D)
MF2: J3.3, Q5.3 (D)
MF3: J3.5, Q6.3 (D)
MF4: J3.7, Q7.3 (D)
MF5: J3.9, Q8.3 (D)
MF6: J3.11, Q9.3 (D)
MF7: J3.13, Q10.3 (D)
MF8: J3.15, Q11.3 (D)
MF9: J3.17, Q12.3 (D)
MF10: J3.19, Q13.3 (D)
MF11: J3.21, Q14.3 (D)
MF12: J3.23, Q15.3 (D)
MF13: J3.25, Q16.3 (D)
MF14: J3.27, Q17.3 (D)
MF15: J3.29, Q18.3 (D)
MF16: J3.31, Q19.3 (D)
MUX_EN: R71.2, U5.6 (INH), U6.6 (INH), U7.6 (INH), U8.6 (INH), U9.6 (INH), U10.6 (INH), U11.6 (INH), U12.6 (INH), U13.6 (INH), U14.6 (INH), U16.L15 (IO13)
MUX_S0: U5.9 (C), U5.10 (B), U5.11 (A), U6.9 (C), U6.10 (B), U6.11 (A), U7.10 (B), U7.11 (A), U10.9 (C), U10.10 (B), U10.11 (A), U11.9 (C), U11.10 (B), U11.11 (A), U12.10 (B), U12.11 (A), U16.L9 (IO25)
MUX_S1: U7.9 (C), U8.9 (C), U8.10 (B), U8.11 (A), U12.9 (C), U13.9 (C), U13.10 (B), U13.11 (A), U16.L10 (IO26)
MUX_S2: U9.10 (B), U9.11 (A), U14.10 (B), U14.11 (A), U16.L11 (IO27)
MUX_S3: U9.9 (C), U14.9 (C), U16.L12 (IO14)
M_L1_0: U10.14 (A COM), U12.5 (CX)
M_L1_1: U10.15 (B COM), U12.3 (CY)
M_L1_2: U10.4 (C COM), U13.12 (AX)
M_L1_3: U11.14 (A COM), U13.13 (AY)
M_L1_4: U11.15 (B COM), U13.2 (BX)
M_L1_5: U11.4 (C COM), U13.1 (BY)
M_L1_6: U12.14 (A COM), U13.5 (CX)
M_L1_7: U12.15 (B COM), U13.3 (CY)
M_L2_0: U12.4 (C COM), U14.12 (AX)
M_L2_1: U13.14 (A COM), U14.13 (AY)
M_L2_2: U13.15 (B COM), U14.2 (BX)
M_L2_3: U13.4 (C COM), U14.1 (BY)
M_L3_0: U14.5 (CX), U14.14 (A COM)
M_L3_1: U14.3 (CY), U14.15 (B COM)
QEN_G: Q2.3 (D), Q3.1 (G), R3.2
QREV_G: D1.2 (A), Q1.1 (G), R1.1
SCL: J5.4, R78.2, U15.10 (SCL), U16.R3 (IO22)
SDA: J5.3, R77.2, U15.9 (SDA), U16.R6 (IO21)
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
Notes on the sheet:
1 Power input
Q1 reverse-polarity MOSFET. ESP32 gets power from USB only.
2 Test current source (LM317T)
I = 1.25 V / R_SET 2.0 ohm = 0.625 A, measured on R_SH
6 ADC (ADS1115, differential)
AIN0-1 contact (PGA 0.256 V), AIN2-3 shunt. 5 V on IO34
7 ESP32 and I/O
GPIO map as docs/design.md
3 Pin select (16 low-side switches)
Qn on = contact n carries the test current
4 Kelvin sense inputs (10k)
10 k series into the muxes
8 Ribbon connectors
34-way IDC to the jack boards
5 Sense muxes (10x CD4053BE, two 16-to-1 trees)
Level 1 S0, level 2 S1, level 3 S2, level 4 S3. Channel n = binary n-1, INH = MUX_EN
